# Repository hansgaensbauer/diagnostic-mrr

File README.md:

# Low Cost MRR For Malaria Diagnosis

This project is a low-cost, low complexity version of the instrument presented by Peng, Chen, and Han in [Development of miniaturized, portable magnetic resonance relaxometry system for point-of-care medical diagnosis](https://aip.scitation.org/doi/citedby/10.1063/1.4754296), used by Peng et al. in [Micromagnetic resonance relaxometry for rapid label-free malaria diagnosis](https://www.nature.com/articles/nm.3622). 

This tool attempts to significantly lower the cost of an instrument capable of diagnosing malaria and other diseases by stripping the researchers' design of all functionality that is not absolutely necessary for this specific application. Notably, this is done by:
1. Modifying the magnet holder so that the separation between the magnets on either side of the sample can be adjusted. This allows the larmor frequency for proton MRR to be tuned to an easily obtaiable frequency. 
2. Generating the CPMG pulse train and the 20MHz carrier with a cheap microcontroller (ATMEGA328P)
3. Replacing COTS RF components with custom implementations using cheap passives and transistors wherever possible
4. Implementing the receiver with tuned filters and peak detect circuits

## New Hardware
These PCBs have been ordered, manufactured, and shipped. They will make testing and calibration much more controlled and repeatable.

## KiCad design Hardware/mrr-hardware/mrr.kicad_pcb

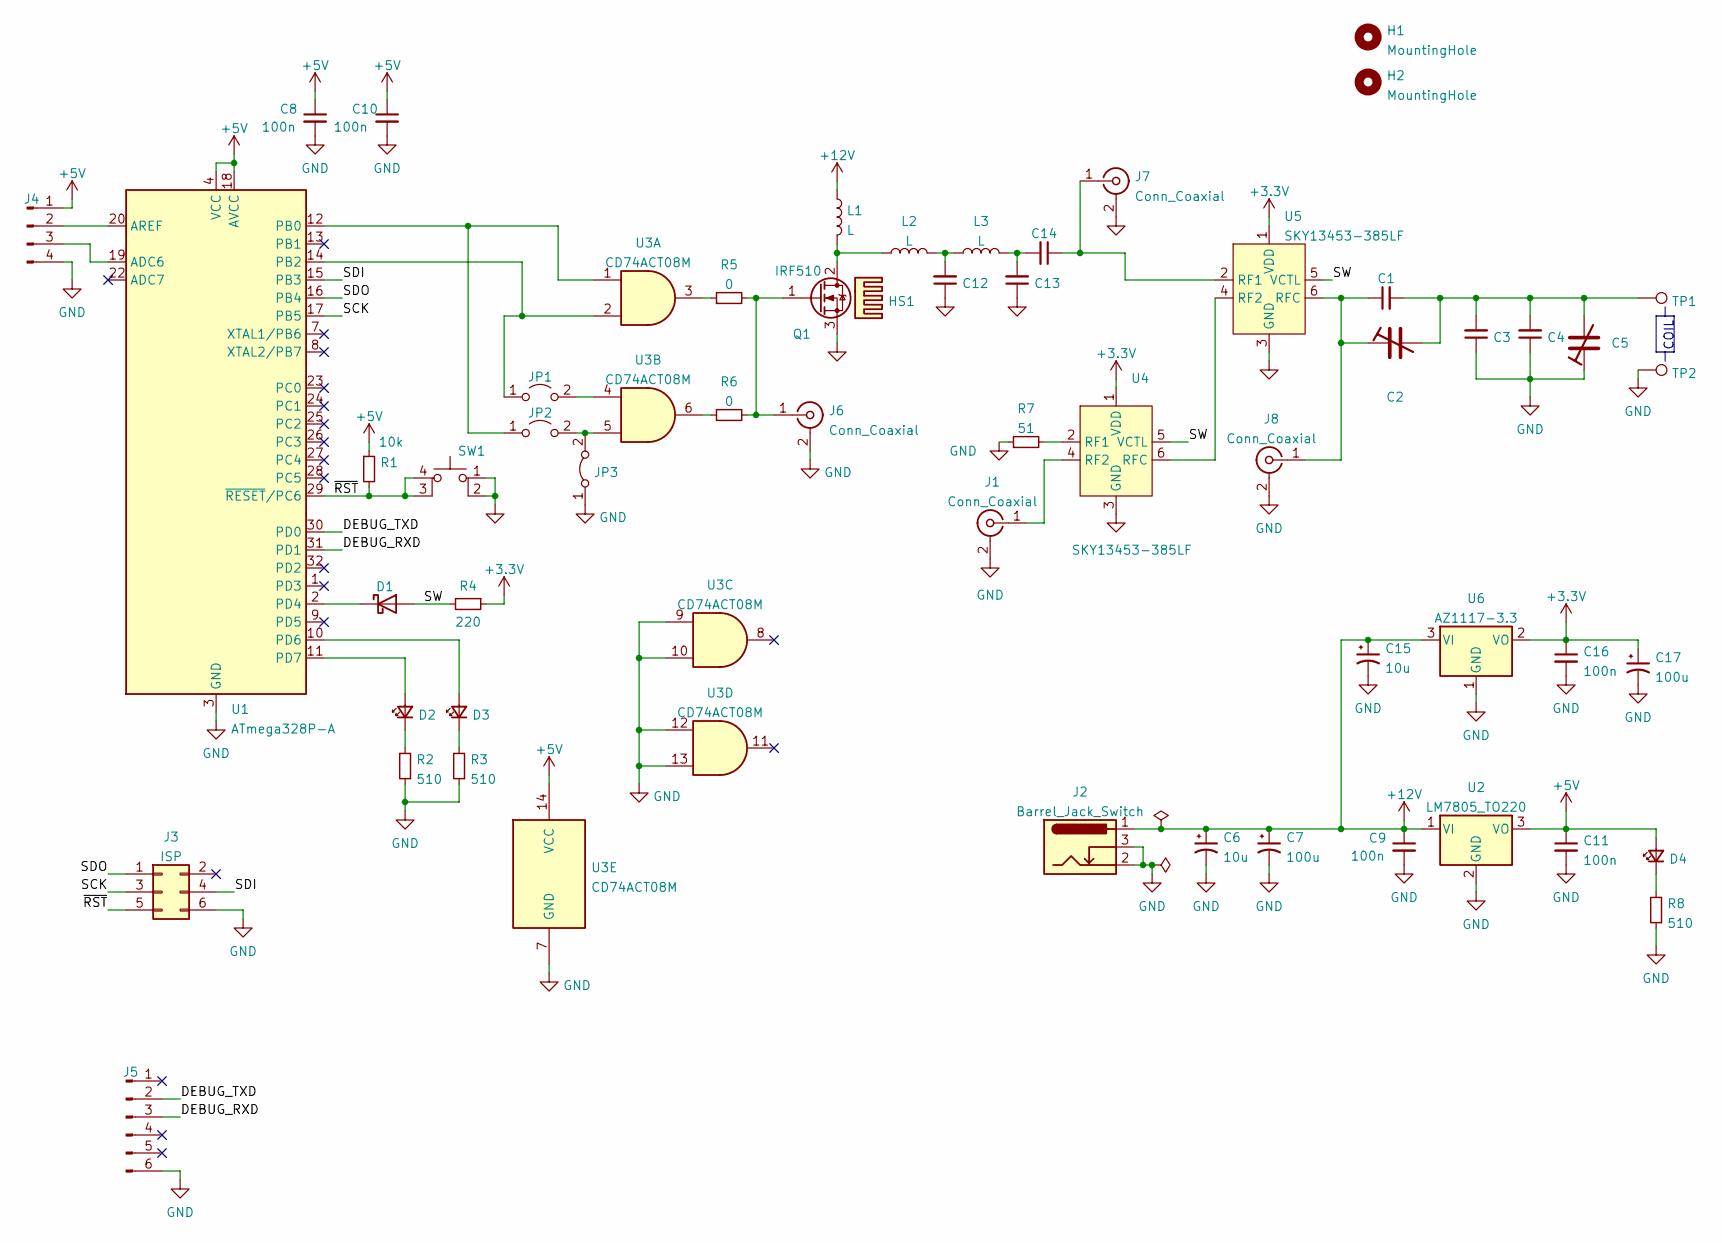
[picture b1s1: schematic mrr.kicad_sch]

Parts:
C1, C3, C4, C12, C13, C14: C_Small; C_0805_2012Metric
C2, C5: C_Trim; C_Trimmer_Sprague-Goodman_SGC3
C6, C15: 10u; CP_Radial_D5.0mm_P2.00mm
C7, C17: 100u; CP_Radial_D6.3mm_P2.50mm
C8, C9, C10, C11, C16: 100n; C_0603_1608Metric
D1: D_Schottky; D_SMB
D2, D3, D4: LED_Small; LED_0805_2012Metric
H1, H2: MountingHole; MountingHole_3.2mm_M3
HS1: Heatsink; BIG_HEATSINK
J1, J6, J7, J8: Conn_Coaxial; SMA_Samtec_SMA-J-P-X-ST-EM1_EdgeMount
J2: Barrel_Jack_Switch; BarrelJack_Wuerth_6941xx301002
J3: ISP; IDC-Header_2x03_P2.54mm_Vertical
J4: Conn_01x04_Male; PinHeader_1x04_P2.54mm_Horizontal
J5: Conn_01x06_Male; PinHeader_1x06_P2.54mm_Horizontal
JP1, JP2: Jumper_2_Open; R_0603_1608Metric
JP3: Jumper_2_Bridged; R_0603_1608Metric
L1, L2, L3: L; L_Toroid_Vertical_L14.7mm_W8.6mm_P5.58mm_Pulse_KM-1
Q1: IRF510; TO-220-3_Vertical
R1: 10k; R_0603_1608Metric
R2, R3, R8: 510; R_0603_1608Metric
R4: 220; R_0603_1608Metric
R5, R6: 0; R_0603_1608Metric
R7: 51; R_0603_1608Metric
SW1: SW_MEC_5E; SW_SPST_Omron_B3FS-100xP
TP1, TP2: TestPoint; TestPoint_Pad_2.0x2.0mm
U1: ATmega328P-A; TQFP-32_7x7mm_P0.8mm
U2: LM7805_TO220; TO-220-3_Vertical
U3: CD74ACT08M; SOIC-14_3.9x8.7mm_P1.27mm
U4, U5: SKY13453-385LF; 6-XFQFN
U6: AZ1117-3.3; SOT-89-3

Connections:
+3V3: C16.1, C17.1, R4.1, U4.1 (VDD), U5.1 (VDD), U6.2 (VO)
+5V: C8.1, C10.1, C11.1, D4.2 (A), J4.1, R1.1, U1.4 (VCC), U1.6 (VCC), U1.18 (AVCC), U2.3 (VO), U3.14 (VCC)
+12V: C6.1, C7.1, C9.1, C15.1, J2.1, L1.1, U2.1 (VI), U6.3 (VI)
/DEBUG_RXD: J5.3, U1.31 (PD1)
/DEBUG_TXD: J5.2, U1.30 (PD0)
/SCK: J3.3, U1.17 (PB5)
/SDI: J3.4, U1.15 (PB3)
/SDO: J3.1, U1.16 (PB4)
/SW: D1.2 (A), R4.2, U4.5 (VCTL), U5.5 (VCTL)
/~RST: J3.5, R1.2, SW1.3 (K), SW1.4 (A), U1.29 (~RESET/PC6)
GND: C3.1, C4.1, C5.1, C6.2, C7.2, C8.2, C9.2, C10.2, C11.2, C12.1, C13.1, C15.2, C16.2, C17.2, J1.2 (Ext), J2.2, J2.3, J3.6, J4.4, J5.6, J6.2 (Ext), J7.2 (Ext), J8.2 (Ext), JP3.1 (A), Q1.3 (S), R2.1, R3.1, R7.1, R8.1, SW1.1, SW1.2, TP2.1, U1.3 (GND), U1.5 (GND), U1.21 (GND), U2.2 (GND), U3.7 (GND), U3.9, U3.10, U3.12, U3.13, U4.3 (GND), U5.3 (GND), U6.1 (GND)
unnamed: C1.1, C2.1, J8.1 (In), U5.6 (RFC)
unnamed: C1.2, C2.2, C3.2, C4.2, C5.2, TP1.1
unnamed: C12.2, L2.2, L3.1
unnamed: C13.2, C14.2, L3.2
unnamed: C14.1, J7.1 (In), U5.2 (RF1)
unnamed: D1.1 (K), U1.2 (PD4)
unnamed: D2.1 (K), R2.2
unnamed: D2.2 (A), U1.11 (PD7)
unnamed: D3.1 (K), R3.2
unnamed: D3.2 (A), U1.10 (PD6)
unnamed: D4.1 (K), R8.2
unnamed: J1.1 (In), U4.4 (RF2)
unnamed: J4.2, U1.20 (AREF)
unnamed: J4.3, U1.19 (ADC6)
unnamed: J6.1 (In), Q1.1 (G), R5.2, R6.2
unnamed: JP1.1 (A), U1.14 (PB2), U3.2
unnamed: JP1.2 (B), U3.4
unnamed: JP2.1 (A), U1.12 (PB0), U3.1
unnamed: JP2.2 (B), JP3.2 (B), U3.5
unnamed: L1.2, L2.1, Q1.2 (D)
unnamed: R5.1, U3.3
unnamed: R6.1, U3.6
unnamed: R7.2, U4.2 (RF1)
unnamed: U4.6 (RFC), U5.4 (RF2)

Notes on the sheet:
COIL

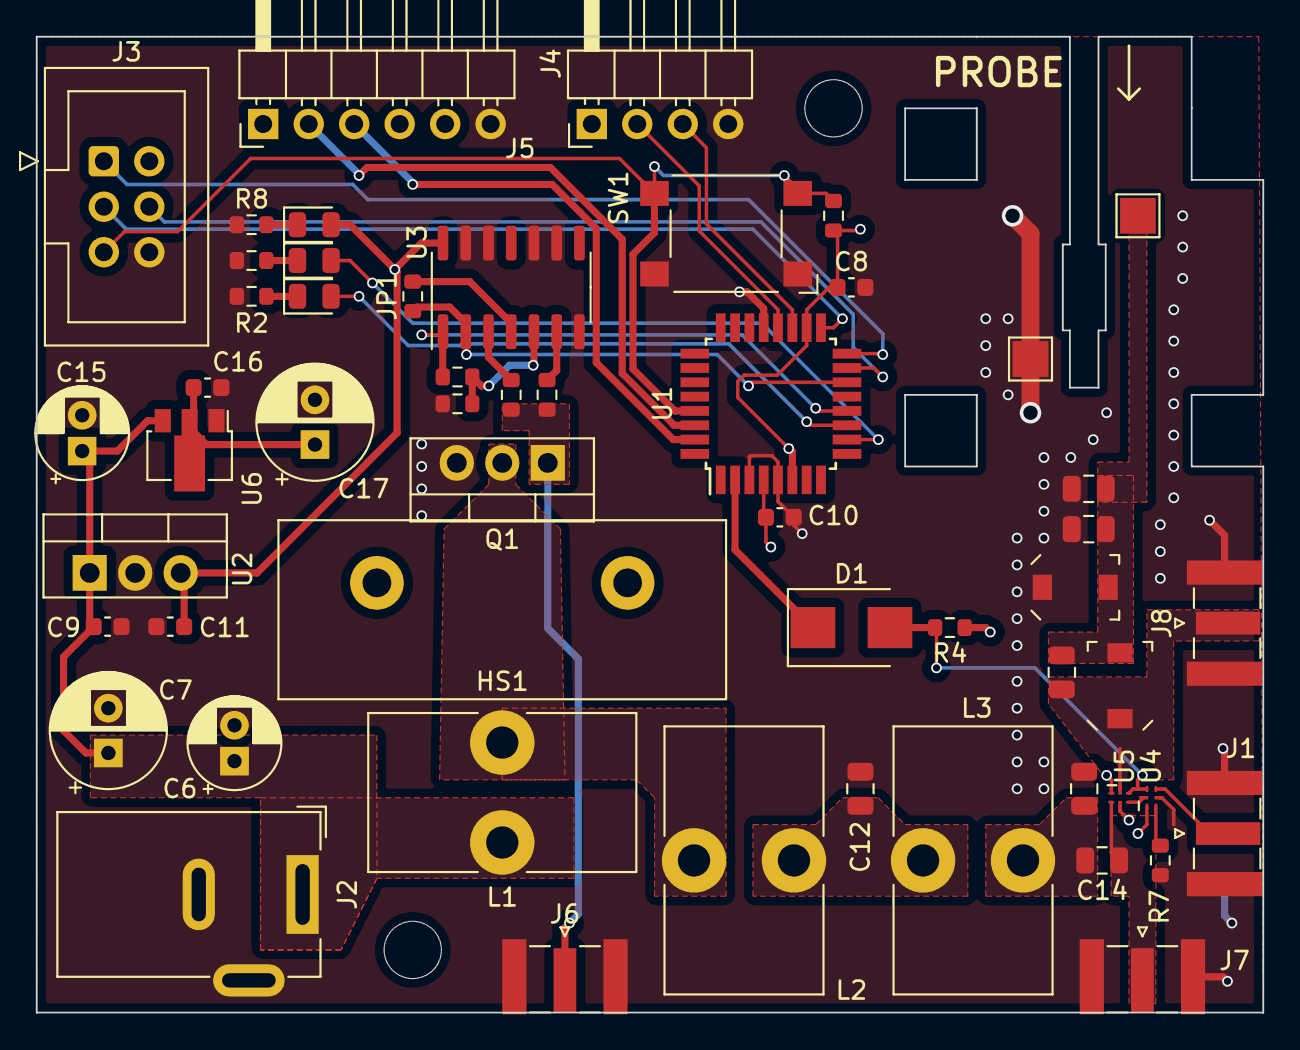
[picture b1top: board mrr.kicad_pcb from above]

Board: 4 copper layers, 68.5 x 54.5 mm, 56 parts (0 on the bottom side), 35 nets.

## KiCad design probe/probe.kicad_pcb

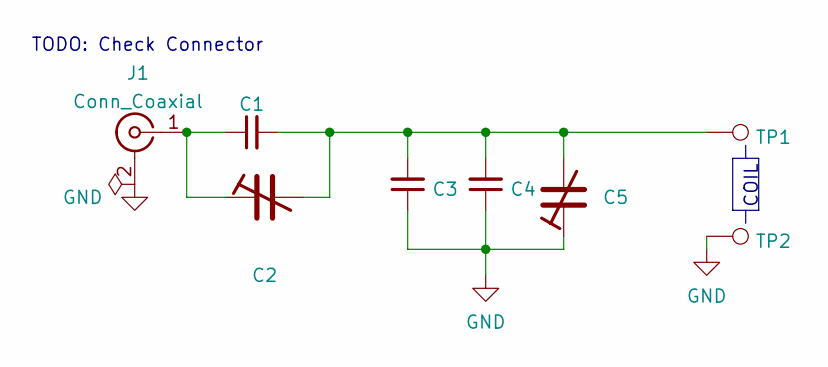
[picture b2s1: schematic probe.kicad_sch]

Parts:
C1, C3, C4: C_Small; C_0805_2012Metric
C2, C5: C_Trim; C_Trimmer_Sprague-Goodman_SGC3
J1: Conn_Coaxial; MMCX_Molex_73415-0961_Horizontal_1.0mm-PCB
TP1, TP2: TestPoint; TestPoint_Pad_2.0x2.0mm

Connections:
GND: C3.1, C4.1, C5.1, J1.2 (Ext), TP2.1
unnamed: C1.1, C2.1, J1.1 (In)
unnamed: C1.2, C2.2, C3.2, C4.2, C5.2, TP1.1

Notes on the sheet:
TODO: Check Connector
COIL

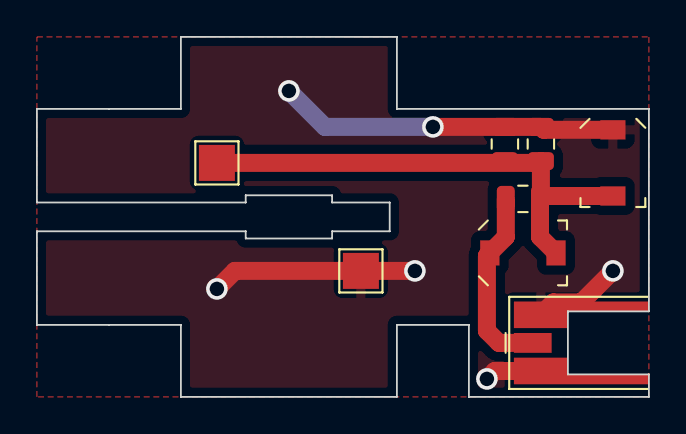
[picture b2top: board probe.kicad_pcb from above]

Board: 2 copper layers, 34.0 x 20.0 mm, 8 parts (0 on the bottom side), 3 nets.

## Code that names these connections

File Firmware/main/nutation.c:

/* Program for determining the 90 and 180 degree pulse lengths
*
* Sweeps through a sequence of 90-180-wait, with a trigger signal
* after the 180 degree wait signal.  
*
* This code uses the fast PWM mode of operation of the 
* 16 bit timer/counter 1 to generate the required pulse
* widths at the desired pulse repetition rate.
*
* This code should be run with FCLK = 20MHz, and CLKO enabled.
* PD4 - RF Switch Control
* PD0 - Trigger Output
* PB2 - Modulation Control
* PB0 - 20MHz Out
*/

#include <avr/io.h>
#include <avr/interrupt.h>
#include <util/delay.h>
#include "mrr.h"

//Pulsewidths to try, in μs
#define NUM_PW 10
uint8_t pulsewidths[NUM_PW] = {10, 20, 30, 40, 50, 60, 70, 80, 90, 100};

//This flag is set after the 180 degree pulse is set up so that the trigger signal
//doesn't fire during the 90 degree pulse
volatile uint8_t echo_ready_flag = 0;

//This flag is used to set up the trigger signal after we enter the echo period
volatile uint8_t trig_ready_flag = 0;

int main(void) {

    //Connect coil to transmiter
    DDRD |= 0b00010001;
    PORTD = 0b00010000;

    TCCR1A = 0b00100011; //Fast PWM, TOP=OCR1A, non inverting for OC1B
    TCCR1B = 0b00011000; //Fast PWM, TOP=OCR1A, CS12:0 = CLK_IO/1.
    DDRB |= 0b00000100; //Set PB2/OC1B to output

    TIMSK1 |= 0b00000110; //Enable Compare A + B Match Interrupts
    sei(); //Enable global interrupts

    //Set up the inter-pulse spacing
    OCR1A = ((PULSETRAIN_DELAY) * (F_CPU / 1000000UL)); //20 cycles/μs * PULSE_SPACINGμs
    

    for(uint8_t i = 0; i < NUM_PW; i++){
        
        trig_ready_flag = 0;
        echo_ready_flag = 0;

	TCCR1A = 0b00100011; 

	//Set up the 90 degree pulse
	echo_ready_flag = 0;
	uint8_t pw_90 = pulsewidths[i];
        OCR1B = ((pw_90) * (F_CPU / 1000000UL)); //90 degree pulse, 20 cycles/μs * 2 * pw_90μs
    
	TCCR1B = 0b00011001; //Fast PWM, TOP=OCR1A, CS12:0 = CLK_IO/1. Turn on timer
    
	//Immediately switch to pulse spacing and 180 degree pulsewidth
        OCR1B = ((pw_90 * 2) * (F_CPU / 1000000UL)); //180 degree pulse, 20 cycles/μs * 2 * pw_90μs

	_delay_ms(1000); //wait one second between repeated trials

	PORTD &= ~0b00000001; //clear the trigger signal
    }

    cli(); //turn off all interrupts

    while (1); //do nothing

}

//Timer 1 Compare B Match Interrupt
//Execute Every time we switch off the RF pulse
ISR(TIMER1_COMPB_vect) {
    PORTD = 0;
    if(echo_ready_flag){
	PORTB &= ~0b00000100; //make sure PB2 stays low
	TCCR1A = 0b00000011; //disconnect OC1B
	trig_ready_flag = 1;
	echo_ready_flag = 0;
    } else {
        echo_ready_flag = 1;
    }
}

//Timer 1 Compare A Match Interrupt
//Execute Every time we switch on the RF coil
ISR(TIMER1_COMPA_vect) {
    if(trig_ready_flag){
	PORTD |= 0b00000001;
        TCCR1B = 0b00011000; //Turn off the timer
	TCNT1 = 0; //Clear the timer
	trig_ready_flag = 0;
    } else{
        PORTD |= 0b00010000;
    }
}

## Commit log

2022-04-01 Initial Commit
    Add existing project files to repo.
2022-04-12 Cal: Start Calibration Firmware [WIP]
2022-04-13 Update Makefile
    Reorganized project to make flashing calibration firmware cleaner
2022-04-13 Move Up Cal
    Rebase Calibration after Makefile Fix
2022-04-13 First Pass Calibration Firmware
2022-04-13 Re-add hardware
2022-04-13 Add stashed changes
2022-04-13 Add new hardware images
